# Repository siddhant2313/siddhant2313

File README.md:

- 👋 Hi, I’m @siddhant2313
- 👀 I’m interested in PCB Designing and Electronics
- 🌱 I’m currently learning Electronics and telecommunication
- I’m looking to collaborate on PCB designing

<!---
siddhant2313/siddhant2313 is a ✨ special ✨ repository because its `README.md` (this file) appears on your GitHub profile.
You can click the Preview link to take a look at your changes.
--->

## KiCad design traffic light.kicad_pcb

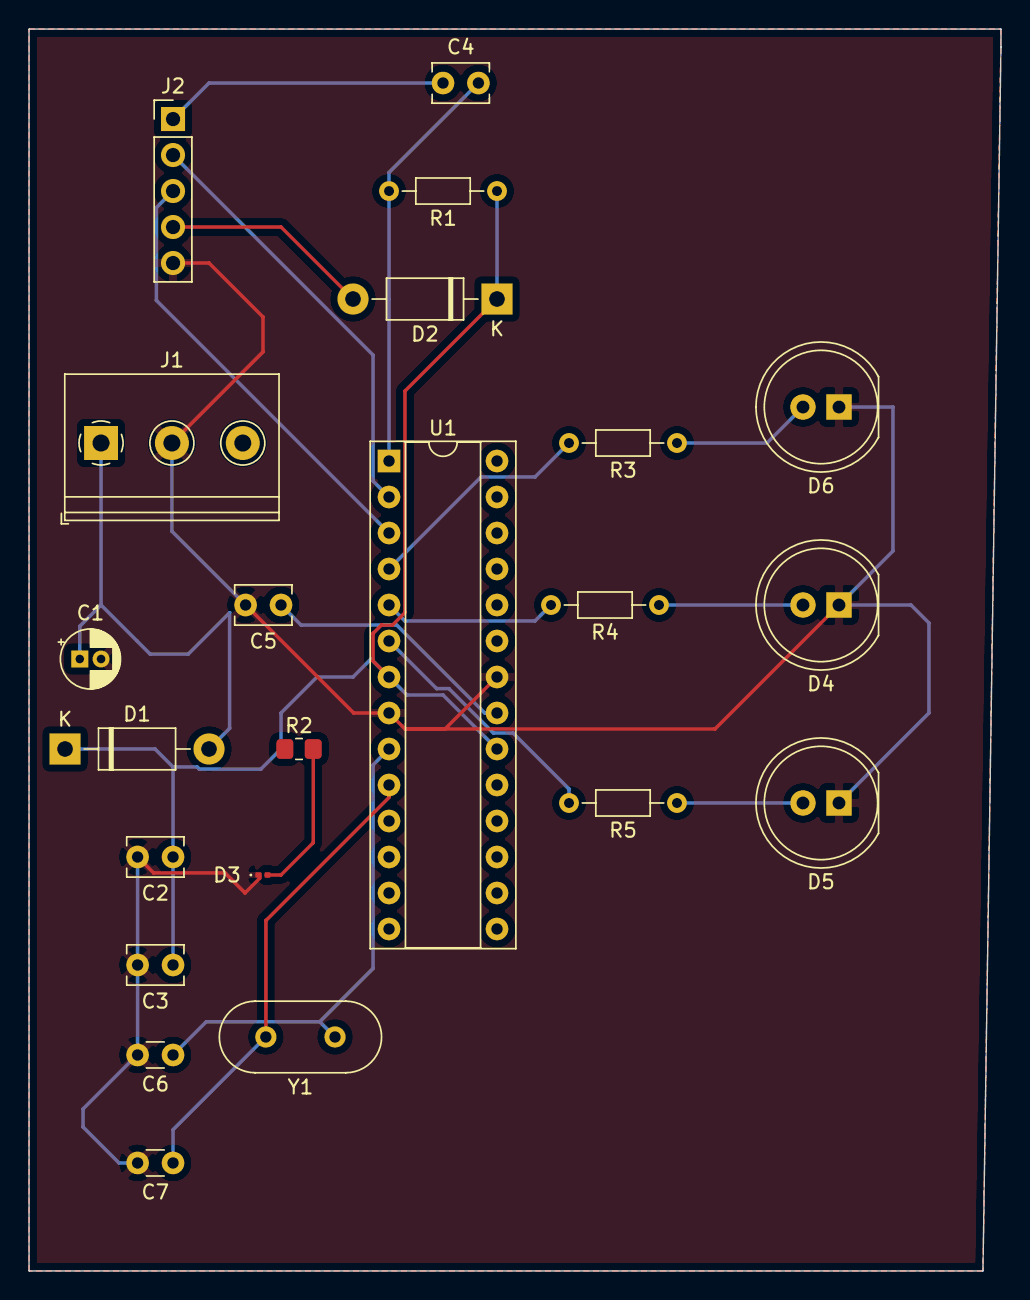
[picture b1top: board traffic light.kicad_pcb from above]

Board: 2 copper layers, 68.6 x 87.6 mm, 22 parts (0 on the bottom side), 18 nets.

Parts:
C1: 10uf; CP_Radial_D4.0mm_P1.50mm
C2, C3, C4, C5: 100nF; C_Disc_D3.8mm_W2.6mm_P2.50mm
C6, C7: 22pf; C_Disc_D3.0mm_W1.6mm_P2.50mm
D1, D2: 1N4007; D_DO-41_SOD81_P10.16mm_Horizontal
D3: LED_Small; LED_0201_0603Metric
D4: amber; LED_D8.0mm
D5: green; LED_D8.0mm
D6: red; LED_D8.0mm
J1: Screw_Terminal_01x02; TerminalBlock_Philmore_TB133_1x03_P5.00mm_Horizontal
J2: Conn_01x05_Male; PinHeader_1x05_P2.54mm_Vertical
R1: R; R_Axial_DIN0204_L3.6mm_D1.6mm_P7.62mm_Horizontal
R2: R_Small; R_0805_2012Metric_Pad1.20x1.40mm_HandSolder
R3, R4: 220R; R_Axial_DIN0204_L3.6mm_D1.6mm_P7.62mm_Horizontal
R5: 330R; R_Axial_DIN0204_L3.6mm_D1.6mm_P7.62mm_Horizontal
U1: ATmega328P-PU; DIP-28_W7.62mm_Socket
Y1: Crystal; Crystal_HC49-4H_Vertical

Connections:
+5V: C1.1, D1.2, J1.1
+5VA: C2.1, C3.1, D1.1, D2.1, R1.1, R2.1, U1.7, U1.20
GND: C1.2, C2.2, C3.2, C5.2, C6.2, C7.2, D3.1, D4.1, D5.1, D6.1, J1.2, J2.5, U1.8, U1.22
unnamed: C4.1, J2.1
unnamed: C5.1, U1.21
unnamed: D2.2, J2.4
unnamed: D3.2, R2.2
unnamed: D4.2, R4.1
unnamed: D5.2, R5.1
unnamed: D6.2, R3.1
Reset: C4.2, R1.2, U1.1
Rx: J2.2, U1.2
Tx: J2.3, U1.3
crystal1: C6.1, U1.9, Y1.1
crystal2: C7.1, U1.10, Y1.2
led1: R3.2, U1.4
led2: R4.2, U1.5
led3: R5.2, U1.6

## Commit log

2021-10-05 Using PiezoElectric Transducer we tried to design a shoe that would charge a voltage storage device depending on the owner's footsteps.
    This will be helpful in an emergency situation where there is problem related to the electricity supply.
2021-10-05 I tried to design a pcb for traffic light system
    Where I used the Atmega328p micro-controller and included UART and crystal for the microcontroller and further created the Gerber file after laying down the tracks for the components used.
